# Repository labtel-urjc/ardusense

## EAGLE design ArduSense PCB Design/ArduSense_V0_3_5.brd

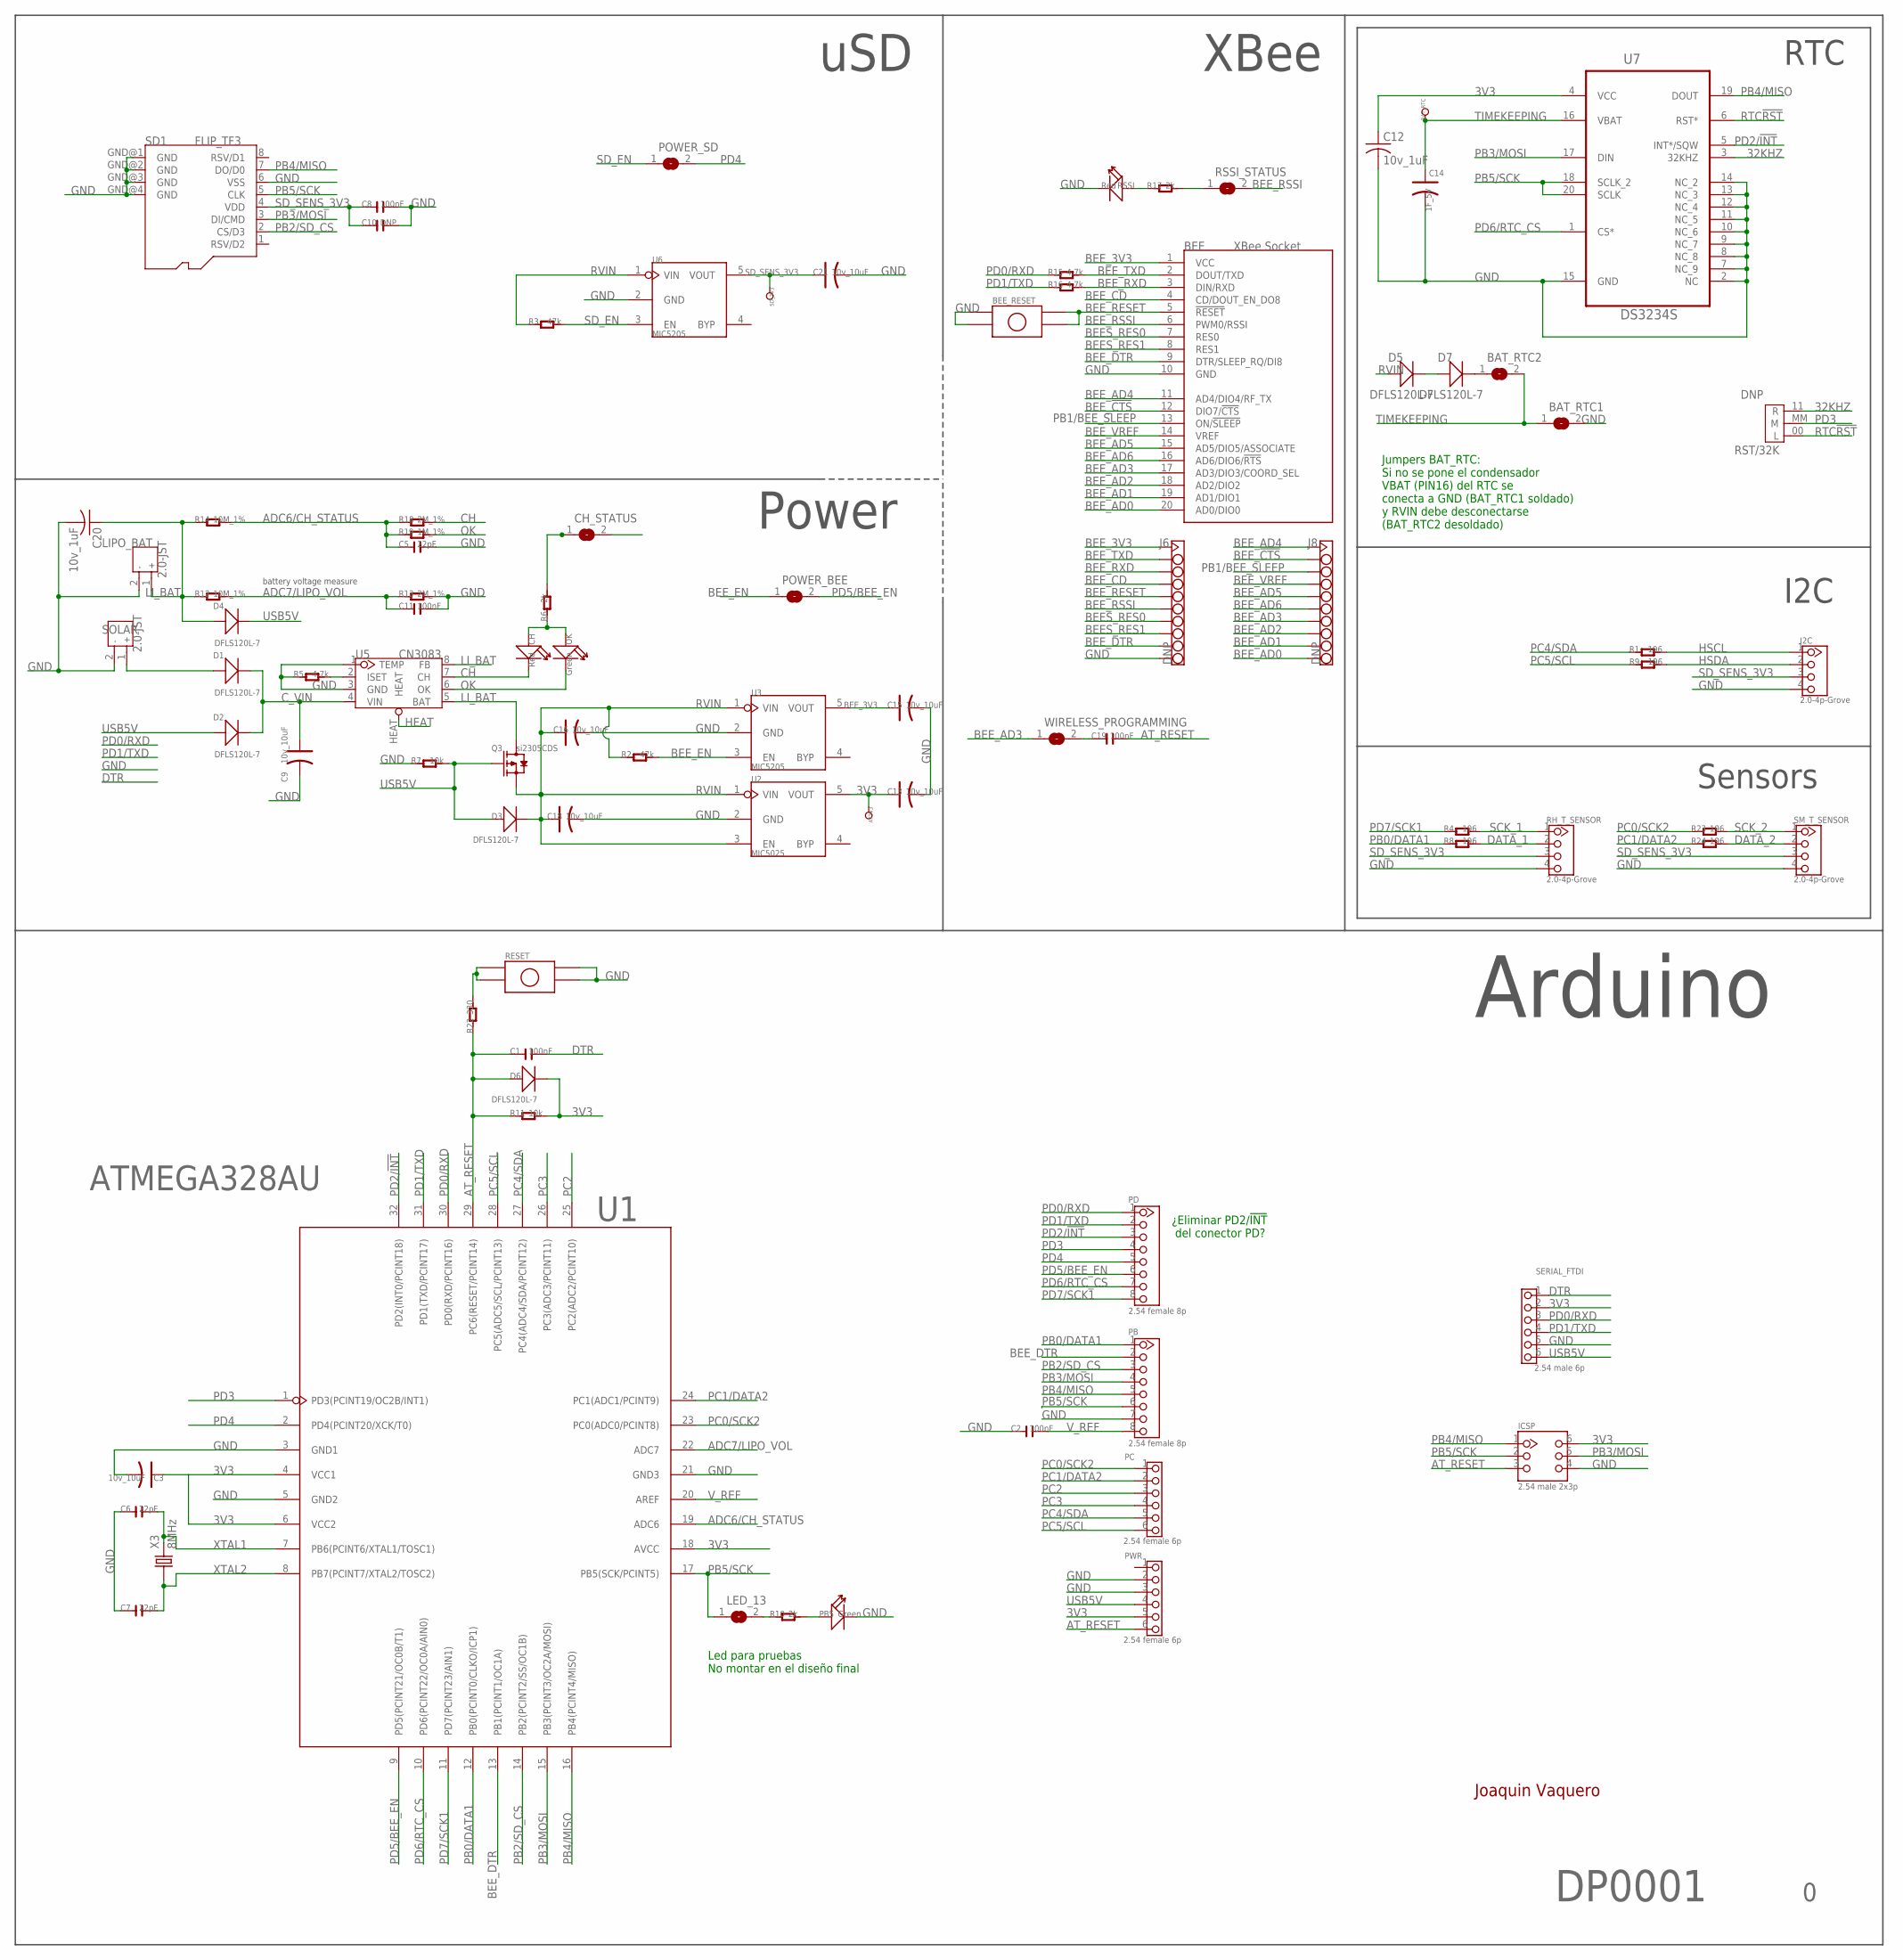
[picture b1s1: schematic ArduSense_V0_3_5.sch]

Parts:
AT3V3: DNP; TP_3535
BAT_RTC: DNP; TP_3535
BAT_RTC1, BAT_RTC2: SJ
BEE: XBee Socket; BEE
BEE_RESET: PUSH_BUTTON; PBUTTON_SMD
C1, C2, C8, C11, C19: 100nF; C1206
C3, C9, C13, C15, C16, C18, C21: 10v_10uF; AVX-A
C5, C6, C7: 22pF; C1206
C10: DNP; C1206
C12, C20: 10v_1uF; C0805
C14: 1F_5V; EB21,5D
CH: Red; D1206
CH_STATUS: SJ
D1, D2, D3, D4, D5, D6, D7: DFLS120L-7; POWERDI123
I2C: 2.0-4p-Grove; 4P-2.0
ICSP: 2.54 male 2x3p; 2X3P-2.54-LEADED
J6, J8: DNP; HEADER_1X10
LED_13: SJ
LIPO_BAT: 2.0-JST; JST-2.0
OK: Green; D1206
PB: 2.54 female 8p; 8P-2.54-LEADED
PB5: Green; D1206
PC: 2.54 female 6p; 6P-2.54-LEADED
PD: 2.54 female 8p; 8P-2.54-LEADED
POWER_BEE: SJ
POWER_SD: SJ
PWR: 2.54 female 6p; 6P-2.54-LEADED
Q3: si2305CDS; SOT23
R1, R4, R8, R9, R23, R24: 196; R1206
R2, R3: 47k; R1206
R5, R15, R16: 4.7k; R1206
R6, R10, R17: 2k; R1206
R7, R11: 10k; R1206
R12, R14: 10M_1%; R1206
R13, R18: 2M_1%; R1206
R19: 1M_1%; R1206
R22: 330; R1206
RESET: PUSH_BUTTON; PBUTTON_SMD
RH_T_SENSOR: 2.0-4p-Grove; 4P-2.0
RSSI: Red; D1206
RSSI_STATUS: SJ
RST/32K: DNP; JUMPER
SD1: FLIP_TF3
SD_3V3: DNP; TP_3535
SERIAL_FTDI: 2.54 male 6p; 6P-2.54-LEADED
SM_T_SENSOR: 2.0-4p-Grove; 4P-2.0
SOLAR: 2.0-JST; JST-2.0
U1: ATMEGA328AU; ATMEGA168-20AU
U2: MIC5025; SOT23-5
U3, U6: MIC5205; SOT23-5
U5: CN3083; SOP8
U7: DS3234S; SOIC127P1032X265-20N
WIRELESS_PROGRAMMING: SJ
X3: 8MHz; HC49UP

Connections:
3V3: AT3V3.T, C3.+ (1), C12.1, C13.+ (1), D6.-, ICSP.6, PWR.5, R11.2, SERIAL_FTDI.2, U1.4 (VCC1), U1.6 (VCC2), U1.18 (AVCC), U2.5 (VOUT), U7.4 (VCC)
32KHZ: RST/32K.11 (R), U7.3 (32KHZ)
ADC6/CH_STATUS: C5.1, R14.2, R18.1, R19.1, U1.19 (ADC6)
ADC7/LIPO_VOL: C11.1, R12.2, R13.1, U1.22 (ADC7)
AT_RESET: C1.1, C19.2, D6.+, ICSP.3, PWR.6, R11.1, R22.1, U1.29 (PC6(RESET/PCINT14))
BEES_RES0: BEE.7 (RES0), J6.7
BEES_RES1: BEE.8 (RES1), J6.8
BEE_3V3: BEE.1 (VCC), C15.+ (1), J6.1, U3.5 (VOUT)
BEE_!CTS: BEE.12 (DIO7/!CTS), J8.2
BEE_AD0: BEE.20 (AD0/DIO0), J8.10
BEE_AD1: BEE.19 (AD1/DIO1), J8.9
BEE_AD2: BEE.18 (AD2/DIO2), J8.8
BEE_AD3: BEE.17 (AD3/DIO3/COORD_SEL), J8.7, WIRELESS_PROGRAMMING.1
BEE_AD4: BEE.11 (AD4/DIO4/RF_TX), J8.1
BEE_AD5: BEE.15 (AD5/DIO5/ASSOCIATE), J8.5
BEE_AD6: BEE.16 (AD6/DIO6/!RTS), J8.6
BEE_CD: BEE.4 (CD/DOUT_EN_DO8), J6.4
BEE_DTR: BEE.9 (DTR/SLEEP_RQ/DI8), J6.9, PB.2, U1.13 (PB1(PCINT1/OC1A))
BEE_EN: POWER_BEE.1, R2.2, U3.3 (EN)
BEE_RESET: BEE.5 (!RESET), BEE_RESET.3, BEE_RESET.4, J6.5
BEE_RSSI: BEE.6 (PWM0/RSSI), J6.6, RSSI_STATUS.2
BEE_RXD: BEE.3 (DIN/RXD), J6.3, R16.2
BEE_TXD: BEE.2 (DOUT/TXD), J6.2, R15.2
BEE_VREF: BEE.14 (VREF), J8.4
CH: CH.-, R18.2, U5.7 (CH)
C_VIN: C9.+ (1), CH_STATUS.2, D1.-, D2.-, U5.4 (VIN)
DATA_1: R8.2, RH_T_SENSOR.2
DATA_2: R24.2, SM_T_SENSOR.2
DTR: C1.2, SERIAL_FTDI.1
GND: BAT_RTC1.2, BEE.10 (GND), BEE_RESET.1, BEE_RESET.2, C2.1, C3.- (2), C5.2, C6.1, C7.1, C8.2, C9.- (2), C10.2, C11.2, C12.6+ (2), C13.- (2), C14.- (2), C15.- (2), C16.- (2), C18.- (2), C20.6+ (2), C21.- (2), I2C.4, ICSP.4, J6.10, LIPO_BAT.2, PB.7, PB5.-, PWR.2, PWR.3, R5.1, R7.1, R13.2, RESET.3, RESET.4, RH_T_SENSOR.4, RSSI.-, SD1.6 (VSS), SD1.GND@1 (GND), SD1.GND@2 (GND), SD1.GND@3 (GND), SD1.GND@4 (GND), SERIAL_FTDI.5, SM_T_SENSOR.4, SOLAR.2, U1.3 (GND1), U1.5 (GND2), U1.21 (GND3), U2.2 (GND), U3.2 (GND), U5.1 (TEMP), U5.3 (GND), U6.2 (GND), U7.2 (NC), U7.7 (NC_9), U7.8 (NC_8), U7.9 (NC_7), U7.10 (NC_6), U7.11 (NC_5), U7.12 (NC_4), U7.13 (NC_3), U7.14 (NC_2), U7.15 (GND)
HEAT: U5.HEAT
HSCL: I2C.1, R1.2
HSDA: I2C.2, R9.2
LI_BAT: C20.1, D4.+, LIPO_BAT.1, Q3.3 (D), R12.1, R14.1, U5.5 (BAT), U5.8 (FB)
unnamed: PB5.+, R10.2
unnamed: D5.-, D7.+
unnamed: D1.+, SOLAR.1
unnamed: R22.2, RESET.1, RESET.2
unnamed: R5.2, U5.2 (ISET)
unnamed: R17.1, RSSI.+
unnamed: R17.2, RSSI_STATUS.1
unnamed: CH.+, OK.+, R6.1
unnamed: BAT_RTC2.1, D7.-
unnamed: C19.1, WIRELESS_PROGRAMMING.2
unnamed: LED_13.2, R10.1
unnamed: CH_STATUS.1, R6.2
OK: OK.-, R19.2, U5.6 (OK)
PB0/DATA1: PB.1, R8.1, U1.12 (PB0(PCINT0/CLKO/ICP1))
PB1/BEE_SLEEP: BEE.13 (ON/!SLEEP), J8.3
PB2/SD_CS: PB.3, SD1.2 (CS/D3), U1.14 (PB2(PCINT2/SS/OC1B))
PB3/MOSI: ICSP.5, PB.4, SD1.3 (DI/CMD), U1.15 (PB3(PCINT3/OC2A/MOSI)), U7.17 (DIN)
PB4/MISO: ICSP.1, PB.5, SD1.7 (DO/D0), U1.16 (PB4(PCINT4/MISO)), U7.19 (DOUT)
PB5/SCK: ICSP.2, LED_13.1, PB.6, SD1.5 (CLK), U1.17 (PB5(SCK/PCINT5)), U7.18 (SCLK_2), U7.20 (SCLK)
PC0/SCK2: PC.1, R23.1, U1.23 (PC0(ADC0/PCINT8))
PC1/DATA2: PC.2, R24.1, U1.24 (PC1(ADC1/PCINT9))
PC2: PC.3, U1.25 (PC2(ADC2/PCINT10))
PC3: PC.4, U1.26 (PC3(ADC3/PCINT11))
PC4/SDA: PC.5, R1.1, U1.27 (PC4(ADC4/SDA/PCINT12))
PC5/SCL: PC.6, R9.1, U1.28 (PC5(ADC5/SCL/PCINT13))
PD0/RXD: PD.1, R15.1, SERIAL_FTDI.3, U1.30 (PD0(RXD/PCINT16))
PD1/TXD: PD.2, R16.1, SERIAL_FTDI.4, U1.31 (PD1(TXD/PCINT17))
PD2/!INT: PD.3, U1.32 (PD2(INT0/PCINT18)), U7.5 (INT*/SQW)
PD3: PD.4, RST/32K.MM (M), U1.1 (PD3(PCINT19/OC2B/INT1))
PD4: PD.5, POWER_SD.2, U1.2 (PD4(PCINT20/XCK/T0))
PD5/BEE_EN: PD.6, POWER_BEE.2, U1.9 (PD5(PCINT21/OC0B/T1))
PD6/RTC_CS: PD.7, U1.10 (PD6(PCINT22/OC0A/AIN0)), U7.1 (CS*)
PD7/SCK1: PD.8, R4.1, U1.11 (PD7(PCINT23/AIN1))
RTC!RST: RST/32K.00 (L), U7.6 (RST*)
RVIN: C16.+ (1), C18.+ (1), D3.-, D5.+, Q3.2 (S), R2.1, R3.1, U2.1 (VIN), U2.3 (EN), U3.1 (VIN), U6.1 (VIN)
SCK_1: R4.2, RH_T_SENSOR.1
SCK_2: R23.2, SM_T_SENSOR.1
SD_EN: POWER_SD.1, R3.2, U6.3 (EN)
SD_SENS_3V3: C8.1, C10.1, C21.+ (1), I2C.3, RH_T_SENSOR.3, SD1.4 (VDD), SD_3V3.T, SM_T_SENSOR.3, U6.5 (VOUT)
TIMEKEEPING: BAT_RTC.T, BAT_RTC1.1, BAT_RTC2.2, C14.+ (1), U7.16 (VBAT)
USB5V: D2.+, D3.+, D4.-, PWR.4, Q3.1 (G), R7.2, SERIAL_FTDI.6
V_REF: C2.2, PB.8, U1.20 (AREF)
XTAL1: C6.2, U1.7 (PB6(PCINT6/XTAL1/TOSC1)), X3.2
XTAL2: C7.2, U1.8 (PB7(PCINT7/XTAL2/TOSC2)), X3.1

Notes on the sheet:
Power
Arduino
uSD
XBee
battery voltage measure
RTC
I2C
DP0001
Jumpers BAT_RTC: Si no se pone el condensador VBAT (PIN16) del RTC se conecta a GND (BAT_RTC1 soldado) y RVIN debe desconectarse (BAT_RTC2 desoldado)
Led para pruebas No montar en el diseño final
¿Eliminar PD2/!INT del conector PD?
Sensors

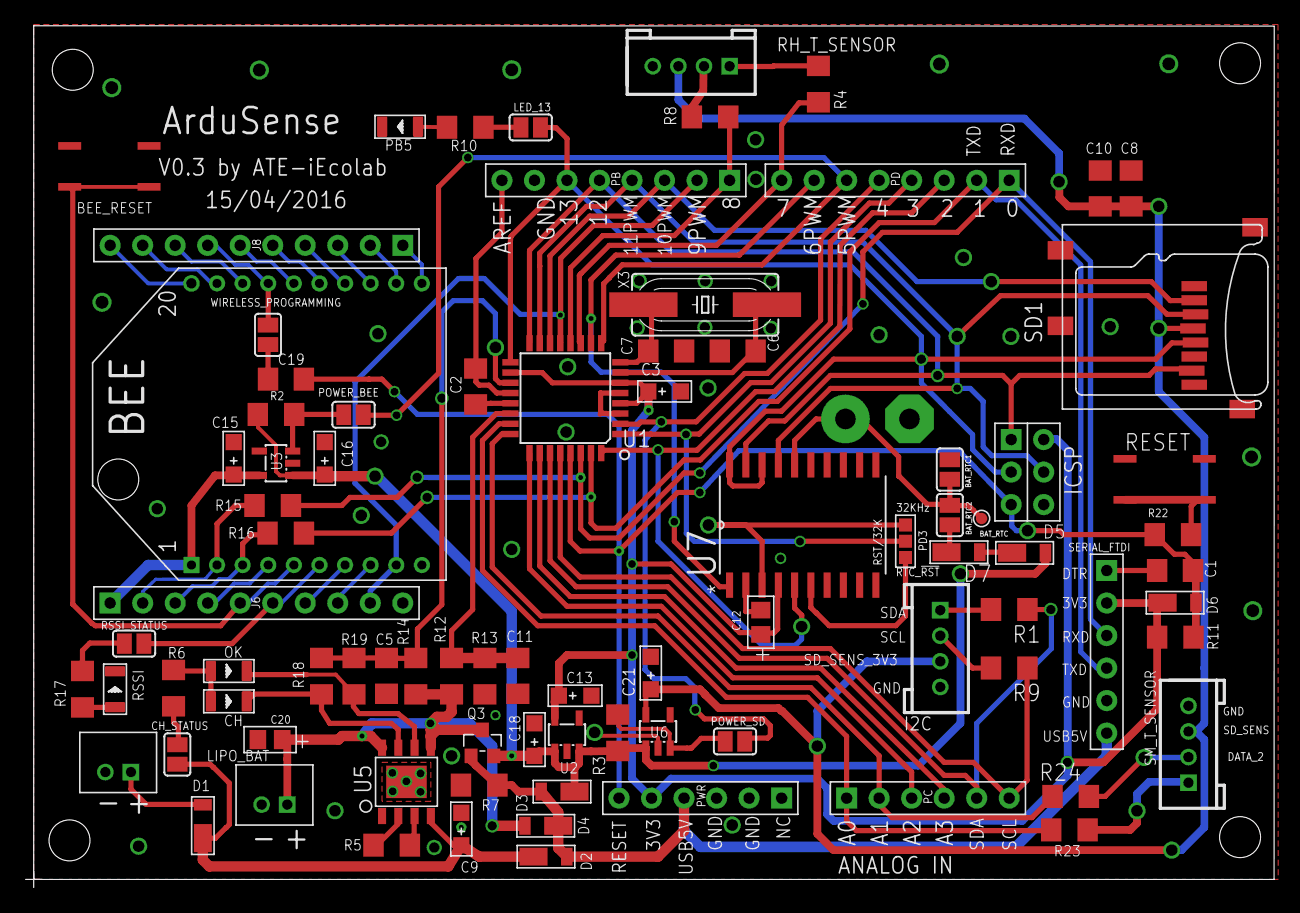
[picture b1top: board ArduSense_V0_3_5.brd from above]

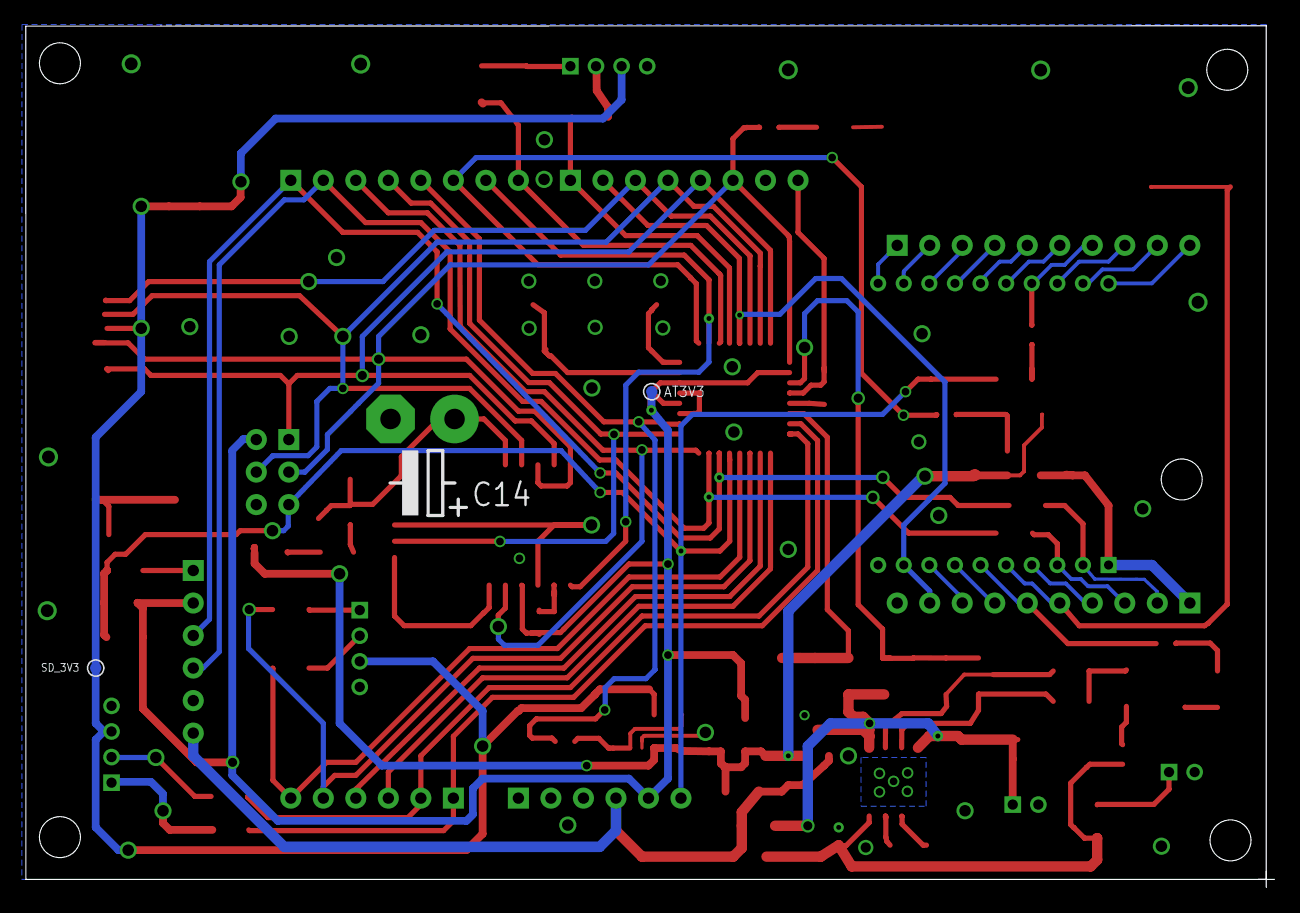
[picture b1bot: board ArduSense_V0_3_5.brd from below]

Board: 2 copper layers, 97.5 x 67.3 mm, 89 parts (3 on the bottom side), 77 nets.

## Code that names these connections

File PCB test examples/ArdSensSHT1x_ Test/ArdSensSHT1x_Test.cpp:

/*Begining of Auto generated code by Atmel studio */
#include <Arduino.h>

/*End of auto generated code by Atmel studio */

/**
 * ReadSHT1xValues
 *
 * Read temperature and humidity values from an SHT1x-series (SHT10,
 * SHT11, SHT15) sensor.
 *
 * Copyright 2009 Jonathan Oxer <jon@oxer.com.au>
 * www.practicalarduino.com
 */

/* Modified 13 February 2014 for ArduSense
   by Joaquín Vaquero
   Electronic Technology Department, Universidad Rey Juan Carlos. Spain.
   */

   
#include <SHT1x.h>
//Beginning of Auto generated function prototypes by Atmel Studio
//End of Auto generated function prototypes by Atmel Studio



// Specify data and clock connections and instantiate SHT1x object for Relative Humidity and Temperature sensor
#define dataPin1  8  // DATA1 - pin 8 on ArduSense as in Pro (PB0, ATmega328 pin 12)
#define clockPin1 7  // SCK2 - pin 7 on ArduSense as in Pro (PD7, ATmega328 pin 11)
SHT1x sht1x1(dataPin1, clockPin1);  // Values for Clock and Data pin to the SHT1x class


// Specify data and clock connections and instantiate SHT1x object for Soil Moisture and Temperature sensor
#define dataPin2  A1  // DATA2 - pin A1 on ArduSense as in Pro (PC1, ATmega328 pin 24)
#define clockPin2 A0  // SCK2 - pin A0 on ArduSense as in Pro (PC0, ATmega328 pin 23)
SHT1x sht1x2(dataPin2, clockPin2);  // Values for Clock and Data pin to the SHT1x class

// Specify data and clock connections and instantiate SHT1x object for Soil Moisture and Temperature sensor
#define ch_status  A6  // CH_SATATU - pin A6 on ArduSense ADC6, ATmega328 pin 19)
#define lipo_vol A7    // LIPO_Vol - pin A7 on ArduSense ADC7, ATmega328 pin 22)

// SD_EN signal. ArduSense: pin 4  PD4, digital pin 
const int SD_Sen_powerEnable = 4;  
// BEE_EN signal. ArduSense: pin 5  PD5, digital pin 
const int BEE_powerEnable = 5;  

void setup()
{
  Serial.begin(115200); // Open serial connection to report values to host
  
  // Configures the power enable control signals as outputs
  pinMode(SD_Sen_powerEnable, OUTPUT);
  pinMode(BEE_powerEnable, OUTPUT);   
  // Enables the power to SD, sensors nad communications modules
  digitalWrite(SD_Sen_powerEnable, HIGH);  
  digitalWrite(BEE_powerEnable, HIGH);  
  
  // Configures the ADC channels ADC6 and ADC7 as analog inputs
  pinMode(ch_status, INPUT);
  pinMode(lipo_vol, INPUT); 
  
  Serial.println("Starting up");
  delay(11);   // Waiting for sensor start up. Needs 11ms to
  // get to Sleep State. No commands must be sent before
  // that time.
}

void loop()
{
  float temp_c1;     // Temperature value, 14 bits resolution, RH & T sensor
  float humidity1;   // Compensated humidity value, 12 bits resolution, RH & T sensor
  float temp_c2;     // Temperature value, 14 bits resolution, SM & T sensor
  float humidity2;   // Compensated humidity value, 12 bits resolution, SM & T sensor

  // Read values from both sensors
  temp_c1 = sht1x1.readTemperatureC();
  humidity1 = sht1x1.readHumidity();
  temp_c2 = sht1x2.readTemperatureC();
  humidity2 = sht1x2.readHumidity();

  // Print the values to the serial port
  Serial.print("Temperature RH & T: ");
  Serial.print(temp_c1, DEC);
  Serial.print("C / Relative Humidity: ");
  Serial.print(humidity1);
  Serial.println("%");
  Serial.print("Temperature SM & T: ");
  Serial.print(temp_c2, DEC);
  Serial.print("C / Soil Moisture: ");
  Serial.print(humidity2);
  Serial.println("%");

  delay(5000);
}

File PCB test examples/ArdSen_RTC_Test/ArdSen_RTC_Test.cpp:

/*Begining of Auto generated code by Atmel studio */
#include <Arduino.h>

/*End of auto generated code by Atmel studio */

/*
 RTC DS3234 test on ArduSense
 	
 The circuit:
 * RTC attached to SPI bus as follows:
 ** CS - pin 6 on ArduSense as in Pro or Pro Mini (PD6, uC pin 10)
 ** MOSI - pin 11 on ArduSense as in Pro or Pro Mini (PB3, uC pin 15)
 ** MISO - pin 12 on ArduSense as in Pro or Pro Mini (PB4, uC pin 16)
 ** CLK - pin 13 on ArduSense as in Pro or Pro Mini (PB5, uC pin 17)
 
 Based on DeadOn RTC - DS3234 Breakout example Sketch
 Available from: https://www.sparkfun.com/products/10160
 Modified 3 February 2014 for ArduSense
 by Joaquín Vaquero
 
 */

#include <SPI.h>
//Beginning of Auto generated function prototypes by Atmel Studio
int RTC_init();
int SetTimeDate(int d, int mo, int y, int h, int mi, int s);
String ReadTimeDate();
//End of Auto generated function prototypes by Atmel Studio



// RTC CS signal. ArduSense: pin 6
const int RTC_chipselect = 6;  
// uSD CS signal. ArduSense: pin 10  
// This is PB2/SS (uC pin 14) 
// Note that even if it's not used as the CS pin, the hardware SS pin 
// must be left as an output or the SPI library functions will not work.
const int SD_chipSelect = 10;

// SPI Master SCK signal at pin 13 (PB5, pin 17 of ATmega328P)
// Output from the uController. RTC as a Slave
// Led attached to this pin
const int SCK_led = 13;
// RTC  PD2/INT* signal. ArduSense: pin 2
// PD2, uC pin 32
const int RTC_INT = 2;

// SD_EN signal. ArduSense: pin 4  PD4, digital pin 
const int SD_Sen_powerEnable = 4;  
// BEE_EN signal. ArduSense: pin 5  PD5, digital pin 
const int BEE_powerEnable = 5;

void setup() {
  Serial.begin(115200);
  
  // Configures the power enable control signals as outputs
  pinMode(SD_Sen_powerEnable, OUTPUT);
  pinMode(BEE_powerEnable, OUTPUT);   
  // Enables the power to SD, sensors nad communications modules
  digitalWrite(SD_Sen_powerEnable, HIGH);  
  digitalWrite(BEE_powerEnable, HIGH);    
  
    // uSD CS signal. ArduSense: pin 10  
  // This is PB2/SS (uC pin 14)// Note that even if it's not used as the CS pin,
  // the hardware SS pin 
  // must be left as an output or the SD library functions will not work. 
  pinMode(SD_chipSelect, OUTPUT);     // change this to 53 on a mega

  RTC_init();  //Initialites RTC DS3234
  // RTC DS3234 time setup. 
  // Day(1-31), month(1-12), year(0-99), hour(0-23), minute(0-59), second(0-59)
  // Day of the week not used.
  SetTimeDate(6,2,14,13,15,16); 
}

void loop() {
  Serial.println(ReadTimeDate());
  delay(1000);               // wait for a second
 
}

// ======== RTC DS 32342 initialization function =====================================
int RTC_init(){ 
  // RTC CS set as an output by default.
  pinMode(RTC_chipselect,OUTPUT);
  // PD2/INT* uC pin set as an input
  // this signal can be a square wave or an INT* signal
  // from RTC, depending on the RTC Control Register
  // configuration.
  pinMode(RTC_INT,INPUT);

  // Start the SPI library:
  SPI.begin();
  // Sets the MSB order for SPI
  SPI.setBitOrder(MSBFIRST); 
  SPI.setDataMode(SPI_MODE1); // Both modes 1 & 3 should work with RTC DS3234. 
                              // Reported problems on Forums with MODE1. We didn`t
                              // have any.
  
  SPI.setClockDivider(SPI_CLOCK_DIV2); // Sets the SPI clock divider relative to the system clock. 
  // Avilable dividers are 2, 4, 8, 16, 32, 64 or 128. 
  // The default setting is SPI_CLOCK_DIV4 sets the SPI clock to one-quarter the frequency 
  // of the system clock (4 Mhz for the boards at 16 MHz).
  // ArduSense has 8 MHz clock, and RTC supports up 4 MHz
  // Changed to SPI_CLOCK_DIV2 to get RTC SPI full speed.
  
  // Set Control Register 
  digitalWrite(RTC_chipselect, LOW);  // Selects RTC
  SPI.transfer(0x8E); // Control Register Address
  // Bit 7:EOSC*=1 Disables Oscillator when battery powered; 
  // Bit 6:BBSQW=1 Enables Battery SQ wave output on INT*/SQW pin;
  // Bit 5:CONV=0 Disable Temperature compensation; 
  // Bit 4-3:RS2-RS1=0-0 Output square wave on INT*/SQW pin at 1Hz; 
  // Bit 2:INTCN=0 Interrupt disabled; 
  // Bit 1-0:A2IE-A1IE=0-0 Alarmans Disabled; 
  // Control Register content=0x60
  SPI.transfer(0x60);
  digitalWrite(RTC_chipselect, HIGH); // Deselects RTC
  delay(10);
}

// ========= RTC DS 32342 Time setup function =========================================
// Day(1-31), month(1-12), year(0-99), hour(0-23), minute(0-59), second(0-59)
int SetTimeDate(int d, int mo, int y, int h, int mi, int s){ 
  int TimeDate [7]={
    s,mi,h,0,d,mo,y  }; // Day of the week not used, set to 0
  for(int i=0; i<=6;i++){
    if(i==3) // Day of the week not used, skipped
      i++;
    int b= TimeDate[i]/10;   // b keeps decens.
    int a= TimeDate[i]-b*10; // a keeps units.
    if(i==2){        // Set de 24/12 Hours mode
      if (b==2)      // Set 24 hour mode
        b=B00000010;   
      else if (b==1) // Set 12 hour mode
        b=B00000001;
    }	
    TimeDate[i]= a+(b<<4);  // Adds units and decens

    digitalWrite(RTC_chipselect, LOW); // Selects RTC
    SPI.transfer(i+0x80); // Timekeeping Registers Address, write mode
    SPI.transfer(TimeDate[i]); // Timekeeping Registers content, write value        
    digitalWrite(RTC_chipselect, HIGH);  // Deselects RTC
  }
}

// ========= RTC DS 32342 Time Read function =========================================
String ReadTimeDate(){
  String temp;
  int TimeDate [7]; // Second,minute,hour,null,day,month,year
                    // Day of the week not used, set to 0		
  for(int i=0; i<=6;i++){
    if(i==3)  // Day of the week not used, skipped
      i++;
    digitalWrite(RTC_chipselect, LOW); // Selects RTC
    SPI.transfer(i+0x00); // Timekeeping Registers Address, read mode
    unsigned int n = SPI.transfer(0x00); // Timekeeping Registers content, read value        
    digitalWrite(RTC_chipselect, HIGH); // Deselects RTC
    int a=n & B00001111;    // a keeps units.
    if(i==2){	
      int b=(n & B00110000)>>4; // Checks bit 5 of the hour register 0x02
      if(b==B00000010)          // If reads 1, 24 hour mode
        b=20;        
      else if(b==B00000001)     // If reads 0, 12 hour mode
        b=10;
      TimeDate[i]=a+b;          // Sets hour data according to the hour mode
    }
    else if(i==4){              // Sets decens for Days
      int b=(n & B00110000)>>4;
      TimeDate[i]=a+b*10;
    }
    else if(i==5){              // Sets decens for Months
      int b=(n & B00010000)>>4;
      TimeDate[i]=a+b*10;
    }
    else if(i==6){              // Sets decens for Years
      int b=(n & B11110000)>>4;
      TimeDate[i]=a+b*10;
    }
    else{	                // Sets decens for Minutes and Seconds
      int b=(n & B01110000)>>4;
      TimeDate[i]=a+b*10;	
    }
  }
  
  //Set time string format as dd/mm/yyyy  hh:mm:ss
  
  if (TimeDate[4]<10) {      // Includes 0 placeholders for single digit values
      temp.concat("0"); }  
  temp.concat(TimeDate[4]);
  temp.concat("/") ;
  if (TimeDate[5]<10) {      // Includes 0 placeholders for single digit values
      temp.concat("0"); }  
  temp.concat(TimeDate[5]);
  temp.concat("/") ;
  temp.concat("20");
  temp.concat(TimeDate[6]);
  temp.concat("     ") ;
 if (TimeDate[2]<10) {      // Includes 0 placeholders for single digit values
      temp.concat("0"); }  
  temp.concat(TimeDate[2]);
  temp.concat(":") ;
 if (TimeDate[1]<10) {      // Includes 0 placeholders for single digit values
      temp.concat("0"); }  
  temp.concat(TimeDate[1]);
  temp.concat(":") ;
 if (TimeDate[0]<10) {      // Includes 0 placeholders for single digit values
      temp.concat("0"); }  
  temp.concat(TimeDate[0]);
  return(temp);
}

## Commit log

2018-04-18 Necessary libraries for project
2018-04-18 Ardusense (arduino) source code
2018-04-18 Revert "Ardusense (arduino) source code"
    This reverts commit 2904e3d80fec815b0102ec733556d5e6e0abcc89.
2018-04-18 source code
    Source code ardusense/arduino
2018-04-27 PCB Test Examples
2018-04-27 Ardusense PCB Design
2018-04-27 Coordinator code - python
2018-07-04 cambio contador bateria
    modificado contador bateria
2018-07-04 añadimos funciones RSSI
    Control de intensidad de señal de comunicaciones
2018-07-04 Cambios RSSI
    Control de intensidad de señal comunicaciones
2018-07-04 cambios finales
    Cambios finales en el código
